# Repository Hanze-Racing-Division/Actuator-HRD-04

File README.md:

# Actuator-HRD-04
Actuator module for shifting

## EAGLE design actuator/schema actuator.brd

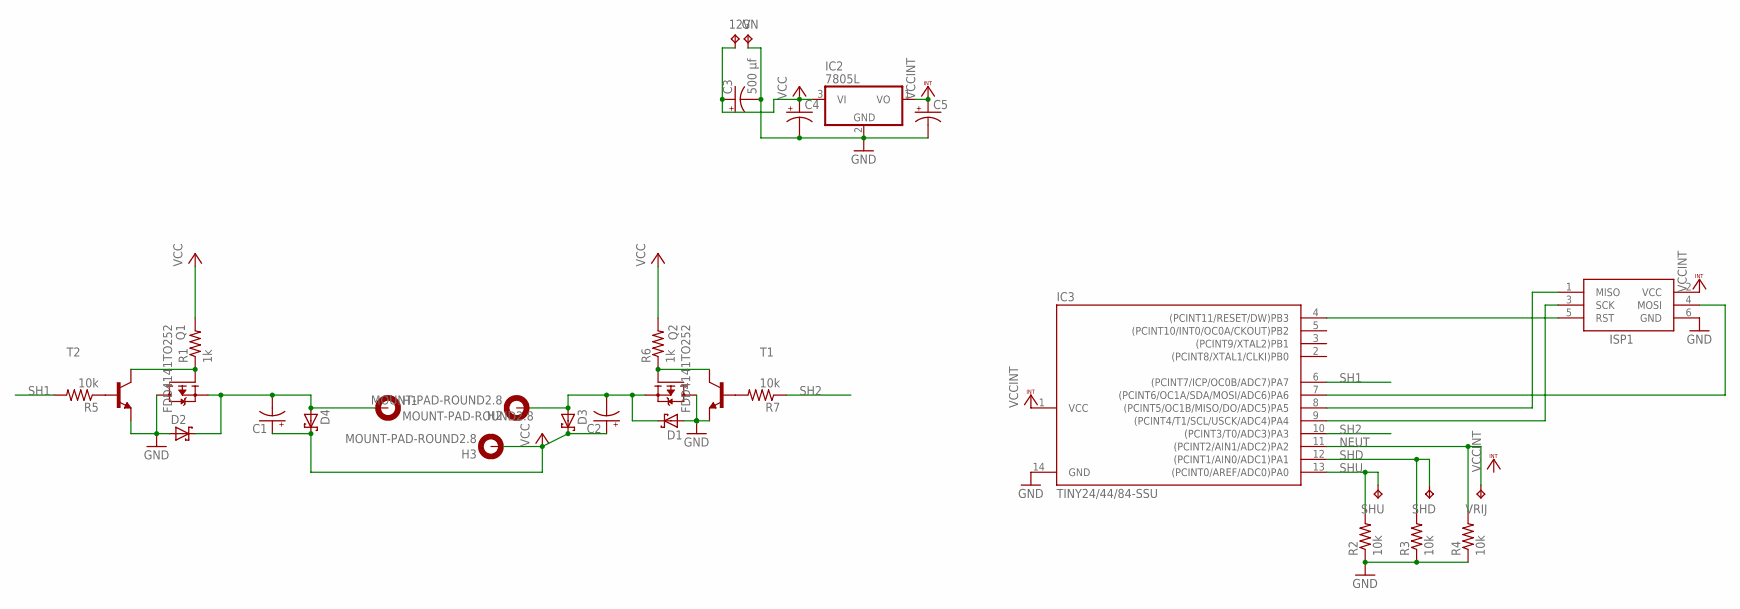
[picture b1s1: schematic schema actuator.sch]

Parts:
12V: TPPAD1-20Y; P1-20Y
C1, C2, C4, C5: CPOL-USD; PANASONIC_D
C3: 500 µf; PANASONIC_G
D1, D2, D3, D4: SCHOTTKY-DIODEDO41; DO41-10
GN: TPPAD1-20Y; P1-20Y
H1, H2, H3: MOUNT-PAD-ROUND2.8; 2,8-PAD
IC2: 7805L; TO92
IC3: TINY24/44/84-SSU; SOIC14
ISP1: AVRISP-6; AVRISP
Q1, Q2: FDD4141TO252; TO252
R1, R6: 1k; R1206
R2, R3, R4, R5, R7: 10k; R1206
SHD: TPPAD1-20Y; P1-20Y
SHU: TPPAD1-20Y; P1-20Y
T1, T2: BC817-40-NPN-SOT23-BEC; SOT23-BEC
VRIJ: TPPAD1-20Y; P1-20Y

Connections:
GND: C3.-, C4.-, C5.-, D1.A, D2.A, GN.TP, IC2.2 (GND), IC3.14 (GND), ISP1.6 (GND), Q1.3 (D), Q2.3 (D), R2.1, R3.1, R4.1, T1.E, T2.E
unnamed: C2.-, D1.C, D3.A, H2.B2,8, Q2.2 (S)
unnamed: Q1.1 (G), R1.1, T2.C
unnamed: Q2.1 (G), R6.1, T1.C
unnamed: R5.1, T2.B
unnamed: C1.-, D2.C, D4.A, H1.B2,8, Q1.2 (S)
unnamed: R7.2, T1.B
unnamed: IC3.7 ((PCINT6/OC1A/SDA/MOSI/ADC6)PA6), ISP1.4 (MOSI)
unnamed: IC3.4 ((PCINT11/RESET/DW)PB3), ISP1.5 (RST)
unnamed: IC3.9 ((PCINT4/T1/SCL/USCK/ADC4)PA4), ISP1.3 (SCK)
unnamed: IC3.8 ((PCINT5/OC1B/MISO/DO/ADC5)PA5), ISP1.1 (MISO)
NEUT: IC3.11 ((PCINT2/AIN1/ADC2)PA2), R4.2, VRIJ.TP
SH1: IC3.6 ((PCINT7/ICP/OC0B/ADC7)PA7), R5.2
SH2: IC3.10 ((PCINT3/T0/ADC3)PA3), R7.1
SHD: IC3.12 ((PCINT1/AIN0/ADC1)PA1), R3.2, SHD.TP
SHU: IC3.13 ((PCINT0/AREF/ADC0)PA0), R2.2, SHU.TP
VCC: 12V.TP, C1.+, C2.+, C3.+, C4.+, D3.C, D4.C, H3.B2,8, IC2.3 (VI), R1.2, R6.2
VCCINT: C5.+, IC2.1 (VO), IC3.1 (VCC), ISP1.2 (VCC)

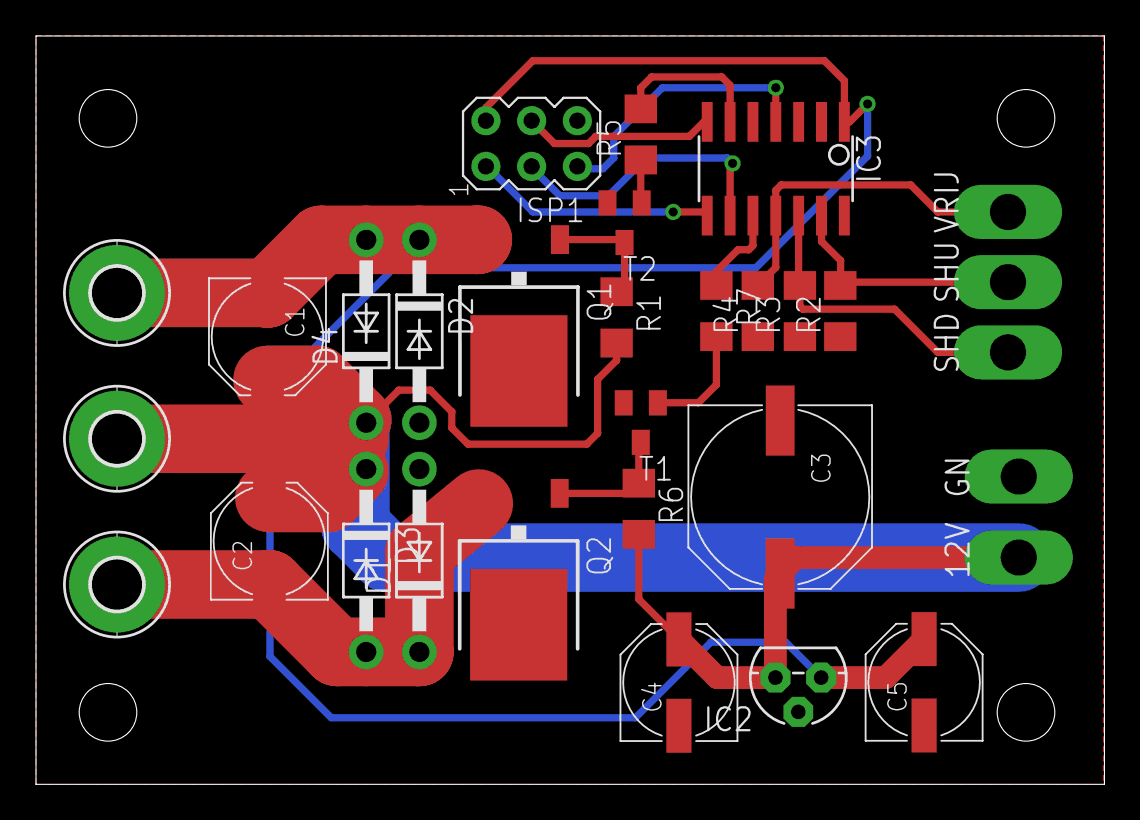
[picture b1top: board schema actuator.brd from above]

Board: 2 copper layers, 59.4 x 41.6 mm, 31 parts (0 on the bottom side), 18 nets.

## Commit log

2016-04-21 added eagle files
